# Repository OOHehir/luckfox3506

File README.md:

# Luckfox3506 KiCad Project

This repository contains the KiCad design files for breadboard friendly adapter board for the LuckFox Core3506 microcontroller module.

## Overview

Hardware design project utilizing KiCad v9 for PCB layout and schematic capture.

## References

- [LuckFox Core3506 Module](https://www.luckfox.com/Core3506)
- [Wiki Page](https://wiki.luckfox.com/Core3506)

## Contents

- Schematic files
- PCB layout files
- Component libraries
- Design documentation

## Requirements

- KiCad 9.0 or later

## Getting Started

1. Clone this repository
2. Open the project files in KiCad
3. Review the schematic and PCB layout

## License

TBD

## Contributing

Contributions are welcome. Please open an issue or submit a pull request.

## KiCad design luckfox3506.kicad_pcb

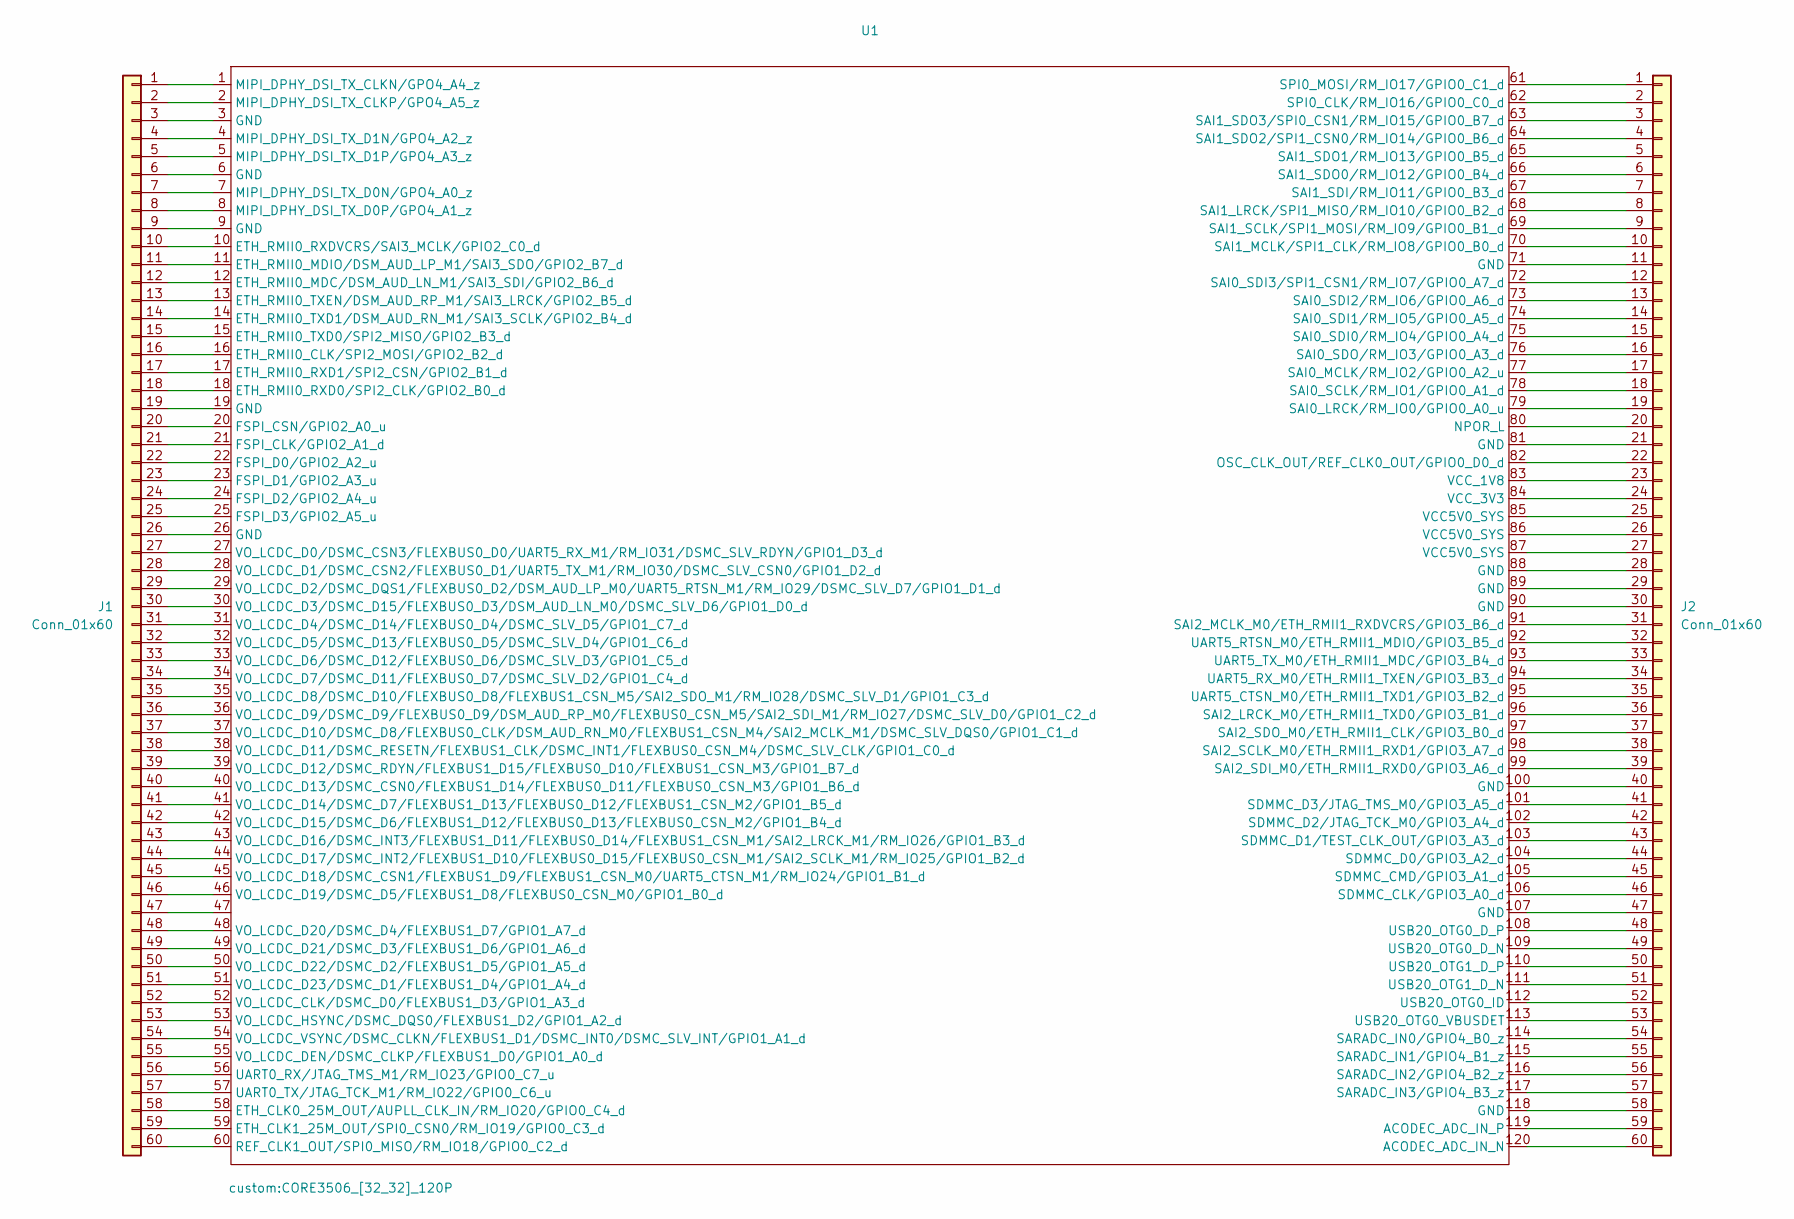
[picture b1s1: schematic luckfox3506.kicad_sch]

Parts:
J1, J2: Conn_01x60; PinHeader_1x60_P2.54mm_Vertical
U1: CORE3506_[32_32]_120P

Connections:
unnamed: J1.1, U1.1 (MIPI_DPHY_DSI_TX_CLKN/GPO4_A4_z)
unnamed: J1.2, U1.2 (MIPI_DPHY_DSI_TX_CLKP/GPO4_A5_z)
unnamed: J1.3, U1.3 (GND)
unnamed: J1.4, U1.4 (MIPI_DPHY_DSI_TX_D1N/GPO4_A2_z)
unnamed: J1.5, U1.5 (MIPI_DPHY_DSI_TX_D1P/GPO4_A3_z)
unnamed: J1.6, U1.6 (GND)
unnamed: J1.7, U1.7 (MIPI_DPHY_DSI_TX_D0N/GPO4_A0_z)
unnamed: J1.8, U1.8 (MIPI_DPHY_DSI_TX_D0P/GPO4_A1_z)
unnamed: J1.9, U1.9 (GND)
unnamed: J1.10, U1.10 (ETH_RMII0_RXDVCRS/SAI3_MCLK/GPIO2_C0_d)
unnamed: J1.11, U1.11 (ETH_RMII0_MDIO/DSM_AUD_LP_M1/SAI3_SDO/G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)
unnamed: J1.12, U1.12 (ETH_RMII0_MDC/DSM_AUD_LN_M1/SAI3_SDI/GP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)
unnamed: J1.13, U1.13 (ETH_RMII0_TXEN/DSM_AUD_RP_M1/SAI3_LRCK/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)
unnamed: J1.14, U1.14 (ETH_RMII0_TXD1/DSM_AUD_RN_M1/SAI3_SCLK/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)
unnamed: J1.15, U1.15 (ETH_RMII0_TXD0/SPI2_MISO/GPIO2_B3_d)
unnamed: J1.16, U1.16 (ETH_RMII0_CLK/SPI2_MOSI/GPIO2_B2_d)
unnamed: J1.17, U1.17 (ETH_RMII0_RXD1/SPI2_CSN/GPIO2_B1_d)
unnamed: J1.18, U1.18 (ETH_RMII0_RXD0/SPI2_CLK/GPIO2_B0_d)
unnamed: J1.19, U1.19 (GND)
unnamed: J1.20, U1.20 (FSPI_CSN/GPIO2_A0_u)
unnamed: J1.21, U1.21 (FSPI_CLK/GPIO2_A1_d)
unnamed: J1.22, U1.22 (FSPI_D0/GPIO2_A2_u)
unnamed: J1.23, U1.23 (FSPI_D1/GPIO2_A3_u)
unnamed: J1.24, U1.24 (FSPI_D2/GPIO2_A4_u)
unnamed: J1.25, U1.25 (FSPI_D3/GPIO2_A5_u)
unnamed: J1.26, U1.26 (GND)
unnamed: J1.27, U1.27 (VO_LCDC_D0/DSMC_CSN3/FLEXBUS0_D0/UART5_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)
unnamed: J1.28, U1.28 (VO_LCDC_D1/DSMC_CSN2/FLEXBUS0_D1/UART5_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)
unnamed: J1.29, U1.29 (VO_LCDC_D2/DSMC_DQS1/FLEXBUS0_D2/DSM_AU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)
unnamed: J1.30, U1.30 (VO_LCDC_D3/DSMC_D15/FLEXBUS0_D3/DSM_AUD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)
unnamed: J1.31, U1.31 (VO_LCDC_D4/DSMC_D14/FLEXBUS0_D4/DSMC_SL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)
unnamed: J1.32, U1.32 (VO_LCDC_D5/DSMC_D13/FLEXBUS0_D5/DSMC_SL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)
unnamed: J1.33, U1.33 (VO_LCDC_D6/DSMC_D12/FLEXBUS0_D6/DSMC_SL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)
unnamed: J1.34, U1.34 (VO_LCDC_D7/DSMC_D11/FLEXBUS0_D7/DSMC_SL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)
unnamed: J1.35, U1.35 (VO_LCDC_D8/DSMC_D10/FLEXBUS0_D8/FLEXBUS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)
unnamed: J1.36, U1.36 (VO_LCDC_D9/DSMC_D9/FLEXBUS0_D9/DSM_AUD_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)
unnamed: J1.37, U1.37 (VO_LCDC_D10/DSMC_D8/FLEXBUS0_CLK/DSM_AU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)
unnamed: J1.38, U1.38 (VO_LCDC_D11/DSMC_RESETN/FLEXBUS1_CLK/DS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)
unnamed: J1.39, U1.39 (VO_LCDC_D12/DSMC_RDYN/FLEXBUS1_D15/FLEX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)
unnamed: J1.40, U1.40 (VO_LCDC_D13/DSMC_CSN0/FLEXBUS1_D14/FLEX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)
unnamed: J1.41, U1.41 (VO_LCDC_D14/DSMC_D7/FLEXBUS1_D13/FLEXBU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)
unnamed: J1.42, U1.42 (VO_LCDC_D15/DSMC_D6/FLEXBUS1_D12/FLEXBU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)
unnamed: J1.43, U1.43 (VO_LCDC_D16/DSMC_INT3/FLEXBUS1_D11/FLEX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)
unnamed: J1.44, U1.44 (VO_LCDC_D17/DSMC_INT2/FLEXBUS1_D10/FLEX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)
unnamed: J1.45, U1.45 (VO_LCDC_D18/DSMC_CSN1/FLEXBUS1_D9/FLEXB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)
unnamed: J1.46, U1.46 (VO_LCDC_D19/DSMC_D5/FLEXBUS1_D8/FLEXBUS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)
unnamed: J1.47, U1.47
unnamed: J1.48, U1.48 (VO_LCDC_D20/DSMC_D4/FLEXBUS1_D7/GPIO1_A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)
unnamed: J1.49, U1.49 (VO_LCDC_D21/DSMC_D3/FLEXBUS1_D6/GPIO1_A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)
unnamed: J1.50, U1.50 (VO_LCDC_D22/DSMC_D2/FLEXBUS1_D5/GPIO1_A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)
unnamed: J1.51, U1.51 (VO_LCDC_D23/DSMC_D1/FLEXBUS1_D4/GPIO1_A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)
unnamed: J1.52, U1.52 (VO_LCDC_CLK/DSMC_D0/FLEXBUS1_D3/GPIO1_A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)
unnamed: J1.53, U1.53 (VO_LCDC_HSYNC/DSMC_DQS0/FLEXBUS1_D2/GPI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)
unnamed: J1.54, U1.54 (VO_LCDC_VSYNC/DSMC_CLKN/FLEXBUS1_D1/DSM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)
unnamed: J1.55, U1.55 (VO_LCDC_DEN/DSMC_CLKP/FLEXBUS1_D0/GPIO1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)
unnamed: J1.56, U1.56 (UART0_RX/JTAG_TMS_M1/RM_IO23/GPIO0_C7_u)
unnamed: J1.57, U1.57 (UART0_TX/JTAG_TCK_M1/RM_IO22/GPIO0_C6_u)
unnamed: J1.58, U1.58 (ETH_CLK0_25M_OUT/AUPLL_CLK_IN/RM_IO20/G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)
unnamed: J1.59, U1.59 (ETH_CLK1_25M_OUT/SPI0_CSN0/RM_IO19/GPIO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)
unnamed: J1.60, U1.60 (REF_CLK1_OUT/SPI0_MISO/RM_IO18/GPIO0_C2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)
unnamed: J2.1, U1.61 (SPI0_MOSI/RM_IO17/GPIO0_C1_d)
unnamed: J2.2, U1.62 (SPI0_CLK/RM_IO16/GPIO0_C0_d)
unnamed: J2.3, U1.63 (SAI1_SDO3/SPI0_CSN1/RM_IO15/GPIO0_B7_d)
unnamed: J2.4, U1.64 (SAI1_SDO2/SPI1_CSN0/RM_IO14/GPIO0_B6_d)
unnamed: J2.5, U1.65 (SAI1_SDO1/RM_IO13/GPIO0_B5_d)
unnamed: J2.6, U1.66 (SAI1_SDO0/RM_IO12/GPIO0_B4_d)
unnamed: J2.7, U1.67 (SAI1_SDI/RM_IO11/GPIO0_B3_d)
unnamed: J2.8, U1.68 (SAI1_LRCK/SPI1_MISO/RM_IO10/GPIO0_B2_d)
unnamed: J2.9, U1.69 (SAI1_SCLK/SPI1_MOSI/RM_IO9/GPIO0_B1_d)
unnamed: J2.10, U1.70 (SAI1_MCLK/SPI1_CLK/RM_IO8/GPIO0_B0_d)
unnamed: J2.11, U1.71 (GND)
unnamed: J2.12, U1.72 (SAI0_SDI3/SPI1_CSN1/RM_IO7/GPIO0_A7_d)
unnamed: J2.13, U1.73 (SAI0_SDI2/RM_IO6/GPIO0_A6_d)
unnamed: J2.14, U1.74 (SAI0_SDI1/RM_IO5/GPIO0_A5_d)
unnamed: J2.15, U1.75 (SAI0_SDI0/RM_IO4/GPIO0_A4_d)
unnamed: J2.16, U1.76 (SAI0_SDO/RM_IO3/GPIO0_A3_d)
unnamed: J2.17, U1.77 (SAI0_MCLK/RM_IO2/GPIO0_A2_u)
unnamed: J2.18, U1.78 (SAI0_SCLK/RM_IO1/GPIO0_A1_d)
unnamed: J2.19, U1.79 (SAI0_LRCK/RM_IO0/GPIO0_A0_u)
unnamed: J2.20, U1.80 (NPOR_L)
unnamed: J2.21, U1.81 (GND)
unnamed: J2.22, U1.82 (OSC_CLK_OUT/REF_CLK0_OUT/GPIO0_D0_d)
unnamed: J2.23, U1.83 (VCC_1V8)
unnamed: J2.24, U1.84 (VCC_3V3)
unnamed: J2.25, U1.85 (VCC5V0_SYS)
unnamed: J2.26, U1.86 (VCC5V0_SYS)
unnamed: J2.27, U1.87 (VCC5V0_SYS)
unnamed: J2.28, U1.88 (GND)
unnamed: J2.29, U1.89 (GND)
unnamed: J2.30, U1.90 (GND)
unnamed: J2.31, U1.91 (SAI2_MCLK_M0/ETH_RMII1_RXDVCRS/GPIO3_B6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)
unnamed: J2.32, U1.92 (UART5_RTSN_M0/ETH_RMII1_MDIO/GPIO3_B5_d)
unnamed: J2.33, U1.93 (UART5_TX_M0/ETH_RMII1_MDC/GPIO3_B4_d)
unnamed: J2.34, U1.94 (UART5_RX_M0/ETH_RMII1_TXEN/GPIO3_B3_d)
unnamed: J2.35, U1.95 (UART5_CTSN_M0/ETH_RMII1_TXD1/GPIO3_B2_d)
unnamed: J2.36, U1.96 (SAI2_LRCK_M0/ETH_RMII1_TXD0/GPIO3_B1_d)
unnamed: J2.37, U1.97 (SAI2_SDO_M0/ETH_RMII1_CLK/GPIO3_B0_d)
unnamed: J2.38, U1.98 (SAI2_SCLK_M0/ETH_RMII1_RXD1/GPIO3_A7_d)
unnamed: J2.39, U1.99 (SAI2_SDI_M0/ETH_RMII1_RXD0/GPIO3_A6_d)
unnamed: J2.40, U1.100 (GND)
unnamed: J2.41, U1.101 (SDMMC_D3/JTAG_TMS_M0/GPIO3_A5_d)
unnamed: J2.42, U1.102 (SDMMC_D2/JTAG_TCK_M0/GPIO3_A4_d)
unnamed: J2.43, U1.103 (SDMMC_D1/TEST_CLK_OUT/GPIO3_A3_d)
unnamed: J2.44, U1.104 (SDMMC_D0/GPIO3_A2_d)
unnamed: J2.45, U1.105 (SDMMC_CMD/GPIO3_A1_d)
unnamed: J2.46, U1.106 (SDMMC_CLK/GPIO3_A0_d)
unnamed: J2.47, U1.107 (GND)
unnamed: J2.48, U1.108 (USB20_OTG0_D_P)
unnamed: J2.49, U1.109 (USB20_OTG0_D_N)
unnamed: J2.50, U1.110 (USB20_OTG1_D_P)
unnamed: J2.51, U1.111 (USB20_OTG1_D_N)
unnamed: J2.52, U1.112 (USB20_OTG0_ID)
unnamed: J2.53, U1.113 (USB20_OTG0_VBUSDET)
unnamed: J2.54, U1.114 (SARADC_IN0/GPIO4_B0_z)
unnamed: J2.55, U1.115 (SARADC_IN1/GPIO4_B1_z)
unnamed: J2.56, U1.116 (SARADC_IN2/GPIO4_B2_z)
unnamed: J2.57, U1.117 (SARADC_IN3/GPIO4_B3_z)
unnamed: J2.58, U1.118 (GND)
unnamed: J2.59, U1.119 (ACODEC_ADC_IN_P)
unnamed: J2.60, U1.120 (ACODEC_ADC_IN_N)

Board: 2 copper layers, 3 parts (1 on the bottom side), 120 nets, no tracks yet.

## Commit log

2025-11-14 Add new footprint
2025-11-14 Initial
2025-11-14 Added
2025-11-14 Added footprints for headers
2025-11-15 Added nets
